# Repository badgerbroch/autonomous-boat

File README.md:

# autonomous-boat
ECE 455 Capstone Project

## Project Roles
Ahmad: Team Lead
Nicolas: Accountant

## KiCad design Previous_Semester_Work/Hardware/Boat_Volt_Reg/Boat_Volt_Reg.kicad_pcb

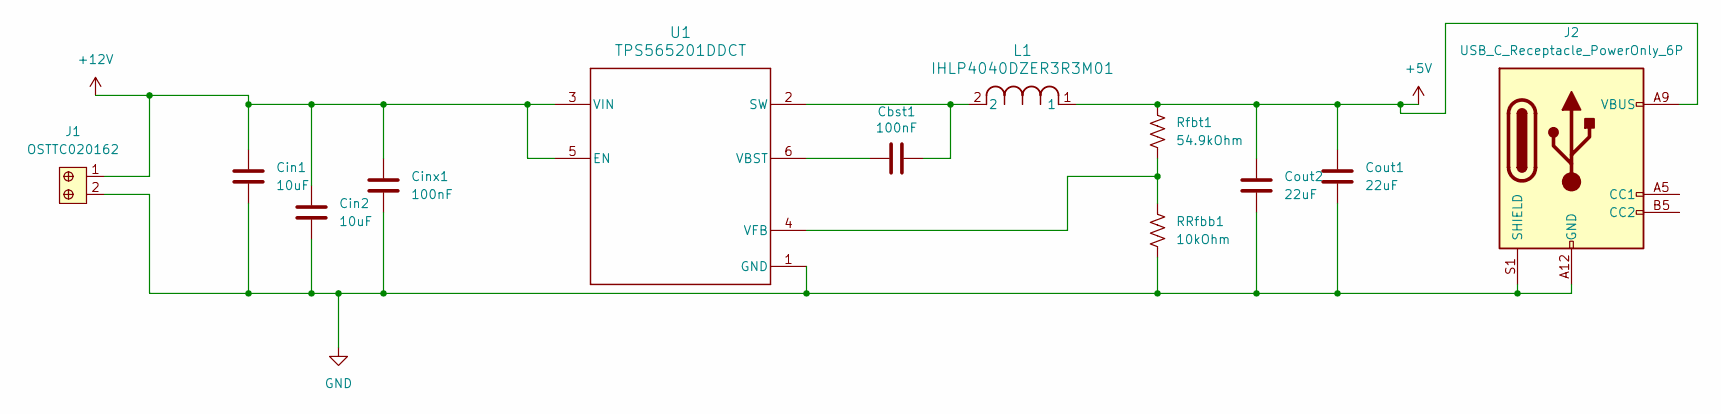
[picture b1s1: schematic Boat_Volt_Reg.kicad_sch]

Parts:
Cbst1: 100nF; C_1206_3216Metric_Pad1.33x1.80mm_HandSolder
Cin1, Cin2: 10uF; C_1206_3216Metric_Pad1.33x1.80mm_HandSolder
Cinx1: 100nF; C_1206_3216Metric_Pad1.33x1.80mm_HandSolder
Cout1, Cout2: 22uF; C_1206_3216Metric_Pad1.33x1.80mm_HandSolder
J1: OSTTC020162; Term_Block_1x2_P5mm; MPN OSTTC020162; Digi-Key_PN ED2600-ND
J2: USB_C_Receptacle_PowerOnly_6P; USB_C_Receptacle_GCT_USB4125-xx-x_6P_TopMnt_Horizontal
L1: IHLP4040DZER3R3M01; IND_IHLP-4040DZ_VIS
RRfbb1: 10kOhm; R_1206_3216Metric_Pad1.30x1.75mm_HandSolder
Rfbt1: 54.9kOhm; R_1206_3216Metric_Pad1.30x1.75mm_HandSolder
U1: TPS565201DDCT; DDC0006A_L

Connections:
+5V: Cout1.1, Cout2.1, J2.A9 (VBUS), J2.B9 (VBUS), L1.1, Rfbt1.1
+12V: Cin1.1, Cin2.1, Cinx1.1, J1.1, U1.3 (VIN), U1.5 (EN)
GND: Cin1.2, Cin2.2, Cinx1.2, Cout1.2, Cout2.2, J1.2, J2.A12 (GND), J2.B12 (GND), J2.S1 (SHIELD), RRfbb1.2, U1.1 (GND)
unnamed: Cbst1.2, L1.2, U1.2 (SW)
unnamed: Cbst1.1, U1.6 (VBST)
unnamed: RRfbb1.1, Rfbt1.2, U1.4 (VFB)

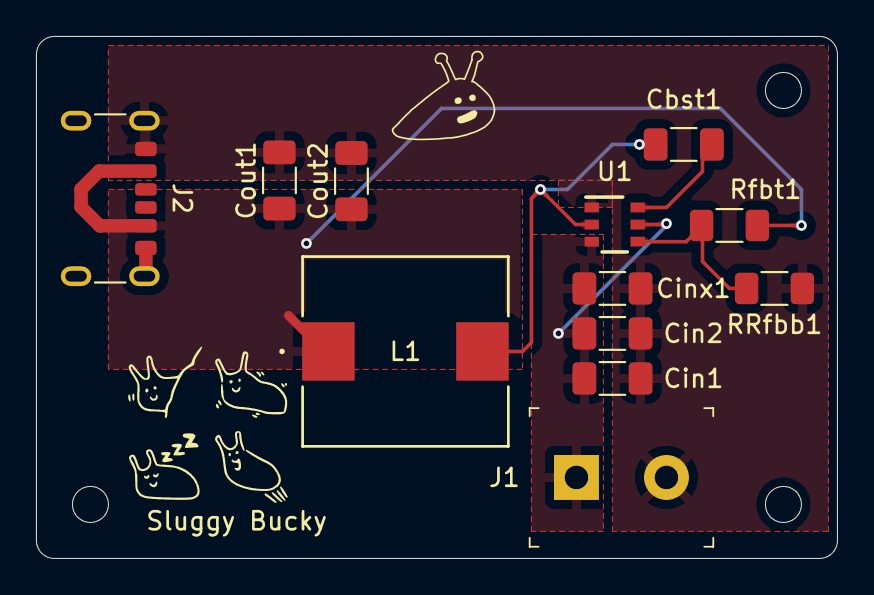
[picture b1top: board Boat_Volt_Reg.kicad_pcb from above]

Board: 2 copper layers, 44.5 x 29.0 mm, 12 parts (0 on the bottom side), 6 nets.

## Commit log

2025-09-10 Added previous semesters work
2025-09-10 this is test commit
2025-09-12 Added requirements file and team roles
2025-09-12 Syntax fix
2025-09-24 Added start of simulation script
2025-09-30 Updated boat sim thrust func with velocity based input and drag equation for calculating motor energy consumption based on desired velocity
2025-09-30 update to battery sim with velocity function for input using measured max velocity from pool test
2025-10-11 Added Reference for 80.20 framing
2025-11-11 Added Visualization for magnetometer data
